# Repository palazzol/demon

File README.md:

# Demon Debugger system - 2.0 coming soon!

Debugger/Monitor for small "computers"

## Vintage Computer Festival Midwest 17 - 2022

- [YouTube](https://youtu.be/M9XML7viIT8)

- [Slides](doc/DD_Presentation-VCFMW_2022.pdf)

## Important Note

**We would like to port this to more systems, and/or help others fix their old things. Please let us know if you need any help getting this system going, should you choose to give it a try!**

## Newly added

* 68HC11 Reference Target - used for Chuck E Cheese Cyberamics computer

## New in version 2.0

* No EPROM programmer needed, reflash through USB serial
* New CPUs supported
  * 6800, 6809
* New targets supported
  * MicroProfessor-1 (Z80 trainer)
  * Heathkit ET-3400(A) (6800 trainer)
  * Heathkit ET-3404 (ET-3400(A) + 6809 adapter) (6809 trainer)
* GUI client
* Python API (alpha) for automating control of targets
* Modularized target code, less work for supporting new targets

## Description

Demon Debugger is a tool that can be used to repair and reverse-engineer devices with 8 and 16 bit CPUs, such as arcade machines, console games, embedded computers, single board computers, etc.  It provides a debugging console, and so is especially useful for systems that lack a working one.

It has been ported to Z80-based, 6502-based, 6800-based, 6809-based, and CP1610-based systems.  There are ports underway to other CPU architectures.

Unfortunately, Demon Debugger can't be used on a totally broken system.  The target system must have a working CPU, and at least a small amount of ROM and RAM.  However, we have found that for most hardware, it's really not too hard to get a system to this point.

## How it Works

In ROM I/O mode, The Demon Debugger board cable plugs into a socket on the target system, in place of a standard JEDEC ROM/EPROM chip.  Then, your PC can communicate with the target over serial, using a standard USB connection.

If your target system is already supported, there will be a target image already built, which you can upload onto your target.  

To support a totally new target system, a small amount of tweaking may need to be done to the assembly code for your target. Generally, if you know the memory map for your system, this is really easy to do.

## More Details

The Demon Debugger system has evolved over time.  If you have a Demon Debugger board, you can use ROM I/O mode with prebuilt target code, and get started right away, without any other tools.  If you need to support a new target, you can still use ROM I/O mode, once you build a new target code.

If you don't have a Demon Debugger board, you can still use the Demon Debugger system in Tethered mode, provided you have a few other capabilities.  It requires only an Arduino Nano/Uno, a single transistor, and the ability to program an EPROM chip.  You need to identify points on your target which can be used (2 outputs, 1 input, and a ground), wire up your modified Arduino accordingly, and modify the communication routines in the target to use those points.  There are a few examples in the repo of doing this.

## Currently Supported Targets

### 6502

* Generic 6502 (Works on most targets) - Atari Asteroids, VCFMW Badge!
* Atari Asteroids Arcade, tethered mode
* Atari Starship 1 Arcade

### 6800

* Heathkit ET-3400(A) (6800 trainer)

### 6809

* Heathkit ET-3404 (ET-3400(A) + 6809 adapter) (6809 trainer)
* Radio Shack Color Computer - Cartridge (6809)

### 6811

* (Chuck E. Cheese Cyberamics Computer) (6811 reference)

### Z80

* Z80 reference code (Tweakable to work on most targets)
* Sega Star Trek Arcade
* Sega Star Trek Arcade, tethered mode
* Bally Midway Gorf Arcade 
* Bally Astrocade, cartridge
* Colecovision/Bit90, cartridge
* Universal Space Raider Arcade
* MicroProfessor-1 (Z80 trainer)

### CP1610

* Mattel Intellivision - via LTO Flash cartridge*

### Other - coming soon

* Mattel Intellivision, via T-Card cartridge (CP1610 target)
* 8080/8085 targets
* Atari 2600 (6502)
* RCA1802 targets
* OS816 SBC (65C816 target)
* TI 99/4A cartridge (TMS9900 target)

## Command Line Client

## GUI Client (WIP)

## API

For now, please see the file demonapi.py

## Old Videos

Tethered Mode - [Sega Sound Board test](https://www.youtube.com/watch?v=uYlbb8uPjoU) Quality is not very good, but the Arduino module is next to the laptop

[Intellivision Demo](https://www.youtube.com/watch?v=_8YfCMpHLhY) Better quality, no Arduino needed using native serialport on the LTO Flash cart.

## 3D Rendering from KiCad

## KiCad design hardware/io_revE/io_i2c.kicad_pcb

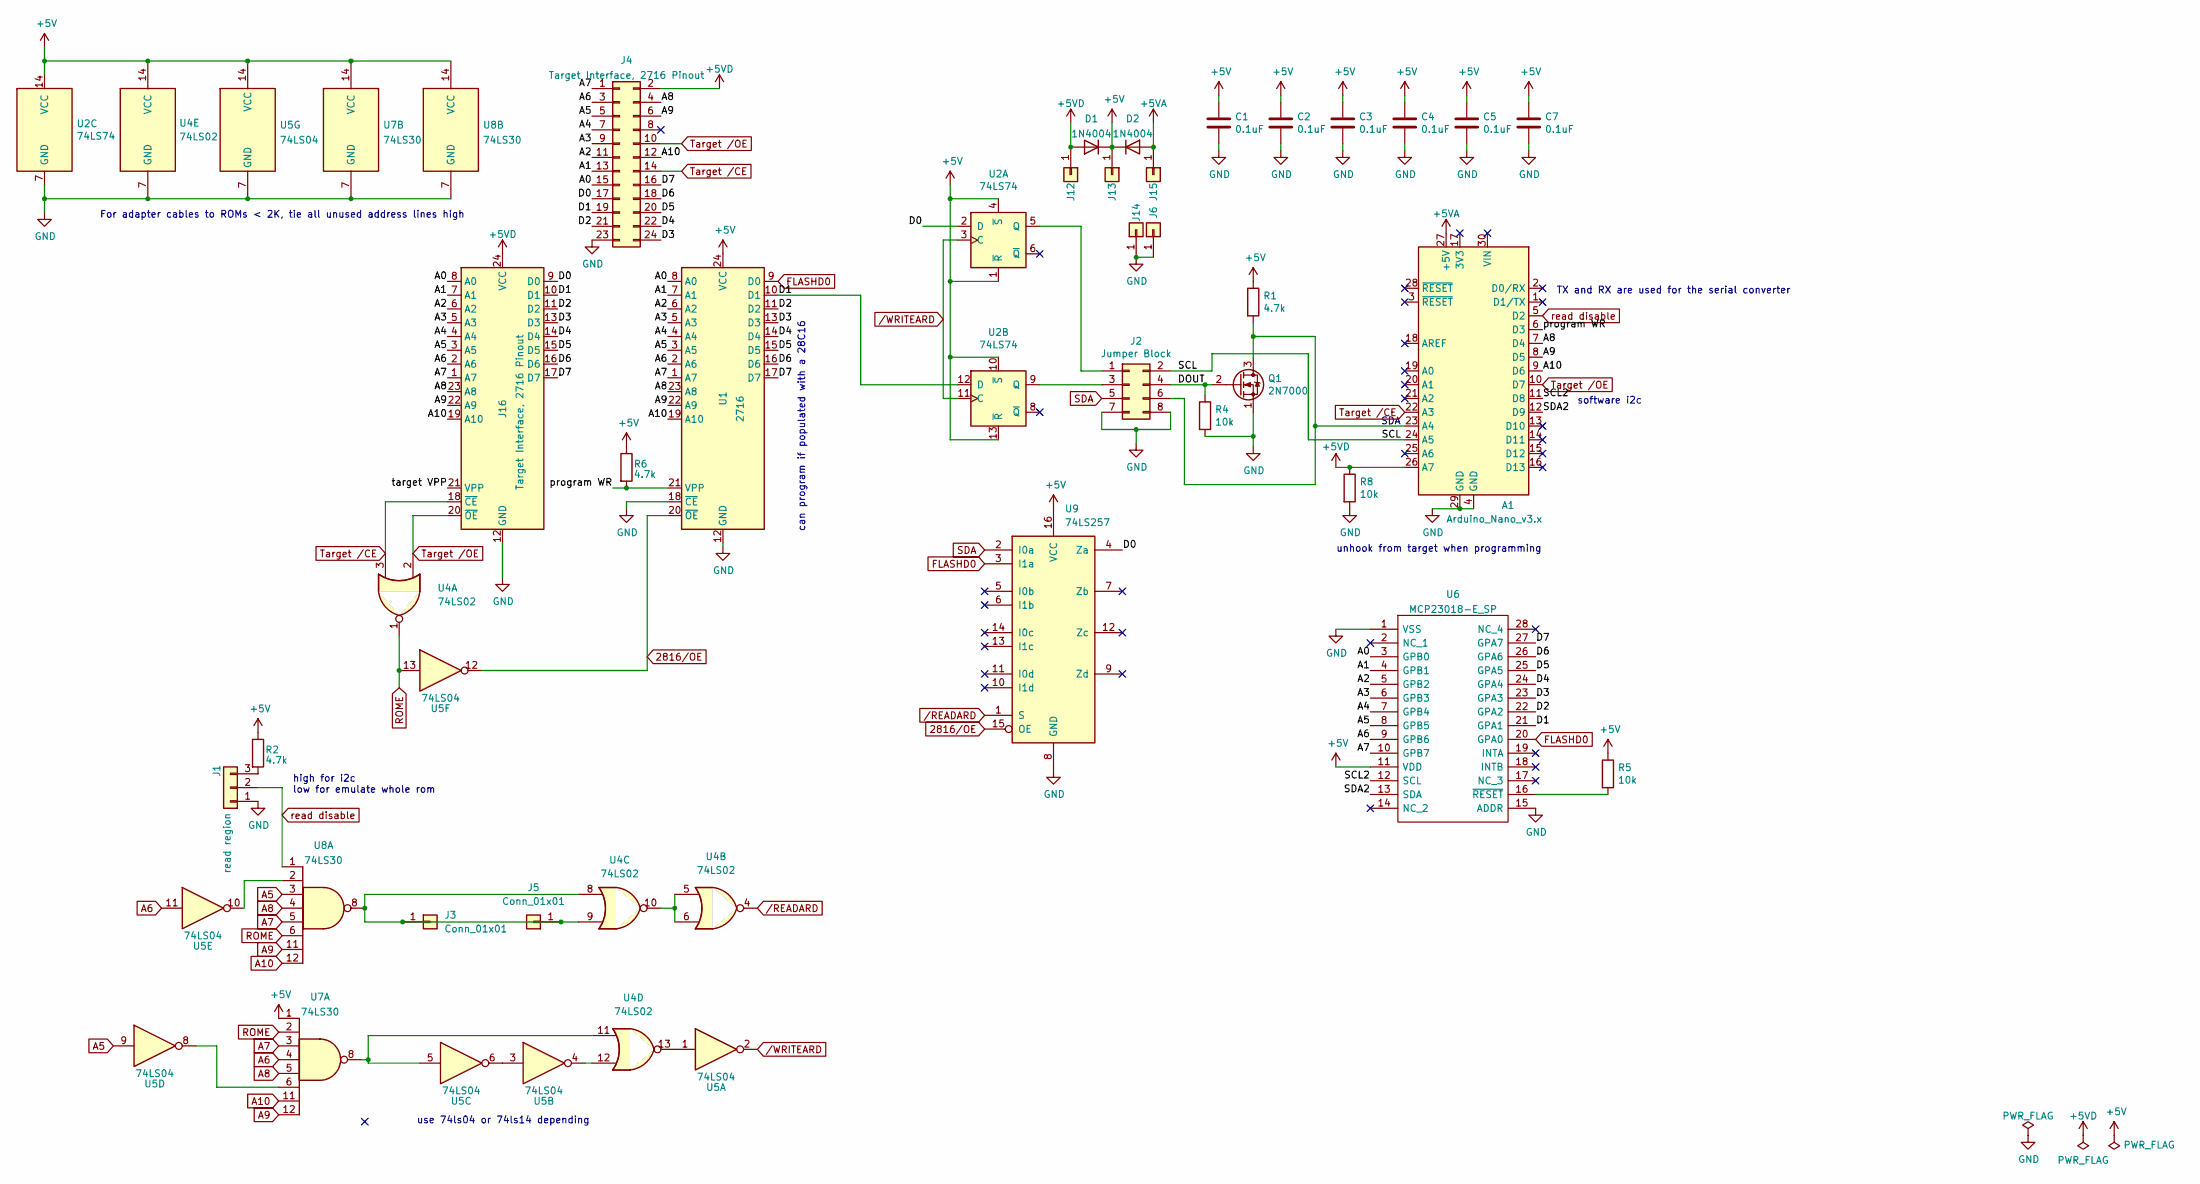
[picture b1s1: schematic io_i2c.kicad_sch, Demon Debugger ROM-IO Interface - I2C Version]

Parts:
A1: Arduino_Nano_v3.x; Arduino_Nano
C1, C2, C3, C4, C5, C7: 0.1uF; C_Axial_L3.8mm_D2.6mm_P7.50mm_Horizontal
D1, D2: 1N4004; D_DO-41_SOD81_P2.54mm_Vertical_AnodeUp
J1: read region; PinHeader_1x03_P2.54mm_Vertical
J2: Jumper Block; PinHeader_2x04_P2.54mm_Vertical
J3, J5, J6, J12, J13, J14, J15: Conn_01x01; PinHeader_1x01_P2.54mm_Vertical
J4: Target Interface, 2716 Pinout; PinHeader_2x12_P2.54mm_Vertical
J16: Target Interface, 2716 Pinout; DIP-24_W15.24mm_Socket
Q1: 2N7000; TO-92_Wide
R1, R2, R6: 4.7k; R_Axial_DIN0207_L6.3mm_D2.5mm_P2.54mm_Vertical
R4, R5, R8: 10k; R_Axial_DIN0207_L6.3mm_D2.5mm_P2.54mm_Vertical
U1: 2716; DIP-24_W15.24mm_Socket
U2: 74LS74; DIP-14_W7.62mm
U4: 74LS02; DIP-14_W7.62mm
U5: 74LS04; DIP-14_W7.62mm
U6: MCP23018-E_SP; DIP-28_W7.62mm; Mouser Part Number 579-MCP23018-E/SP
U7, U8: 74LS30; DIP-14_W7.62mm
U9: 74LS257; DIP-16_W7.62mm

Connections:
2816/OE: U1.20 (~OE), U5.12, U9.15 (OE)
+5V: C1.1, C2.1, C3.1, C4.1, C5.1, C7.1, D1.1 (K), D2.1 (K), J13.1 (Pin_1_1), R1.1, R2.1, R5.1, R6.1, U1.24 (VCC), U2.1 (~R), U2.4 (~S), U2.10 (~S), U2.13 (~R), U2.14 (VCC), U4.14 (VCC), U5.14 (VCC), U6.11 (VDD), U7.1, U7.14 (VCC), U8.14 (VCC), U9.16 (VCC)
+5VA: A1.27 (+5V), D2.2 (A), J15.1 (Pin_1_1)
+5VD: A1.26 (A7), D1.2 (A), J4.2, J12.1 (Pin_1_1), J16.24 (VCC), R8.1
/A0: J4.15, J16.8 (A0), U1.8 (A0), U6.3 (GPB0)
/A1: J4.13, J16.7 (A1), U1.7 (A1), U6.4 (GPB1)
/A2: J4.11, J16.6 (A2), U1.6 (A2), U6.5 (GPB2)
/A3: J4.9, J16.5 (A3), U1.5 (A3), U6.6 (GPB3)
/A4: J4.7, J16.4 (A4), U1.4 (A4), U6.7 (GPB4)
/D0: J4.17, J16.9 (D0), U2.2 (D), U9.4 (Za)
/D1: J4.19, J16.10 (D1), U1.10 (D1), U2.12 (D), U6.21 (GPA1)
/D2: J4.21, J16.11 (D2), U1.11 (D2), U6.22 (GPA2)
/D3: J4.24, J16.13 (D3), U1.13 (D3), U6.23 (GPA3)
/D4: J4.22, J16.14 (D4), U1.14 (D4), U6.24 (GPA4)
/D5: J4.20, J16.15 (D5), U1.15 (D5), U6.25 (GPA5)
/D6: J4.18, J16.16 (D6), U1.16 (D6), U6.26 (GPA6)
/D7: J4.16, J16.17 (D7), U1.17 (D7), U6.27 (GPA7)
/DOUT: J2.4, Q1.2 (G), R4.1
/SCL: A1.24 (A5), J2.2
/SCL2: A1.11 (D8), U6.12 (SCL)
/SDA2: A1.12 (D9), U6.13 (SDA)
/program WR: A1.6 (D3), R6.2, U1.21 (VPP)
/target VPP: J16.21 (VPP)
A5: J4.5, J16.3 (A5), U1.3 (A5), U5.9, U6.8 (GPB5), U8.3
A6: J4.3, J16.2 (A6), U1.2 (A6), U5.11, U6.9 (GPB6), U7.4
A7: J4.1, J16.1 (A7), U1.1 (A7), U6.10 (GPB7), U7.3, U8.5
A8: A1.7 (D4), J4.4, J16.23 (A8), U1.23 (A8), U7.5, U8.4
A9: A1.8 (D5), J4.6, J16.22 (A9), U1.22 (A9), U7.12, U8.11
A10: A1.9 (D6), J4.12, J16.19 (A10), U1.19 (A10), U7.11, U8.12
FLASHD0: U1.9 (D0), U6.20 (GPA0), U9.3 (I1a)
GND: A1.4 (GND), A1.29 (GND), C1.2, C2.2, C3.2, C4.2, C5.2, C7.2, J1.1, J2.7, J2.8, J4.23, J6.1 (Pin_1_1), J14.1 (Pin_1_1), J16.12 (GND), Q1.1 (S), R4.2, R8.2, U1.12 (GND), U1.18 (~CE), U2.7 (GND), U4.7 (GND), U5.7 (GND), U6.1 (VSS), U6.15 (ADDR), U7.7 (GND), U8.7 (GND), U9.8 (GND)
unnamed: A1.23 (A4), J2.6, Q1.3 (D), R1.2
unnamed: J1.3, R2.2
unnamed: J2.1, U2.5 (Q)
unnamed: J2.3, U2.9 (Q)
unnamed: J3.1 (Pin_1_1), J5.1 (Pin_1_1), U4.8, U4.9, U8.8
unnamed: U4.5, U4.6, U4.10
unnamed: U4.11, U5.5, U7.8
unnamed: U4.12, U5.4
unnamed: U4.13, U5.1
unnamed: U5.3, U5.6
unnamed: U5.8, U7.6
unnamed: U5.10, U8.2
unnamed: R5.2, U6.16 (~RESET)
ROME: U4.1, U5.13, U7.2, U8.6
SDA: J2.5, U9.2 (I0a)
Target /CE: A1.22 (A3), J4.14, J16.18 (~CE), U4.3
Target /OE: A1.10 (D7), J4.10, J16.20 (~OE), U4.2
read disable: A1.5 (D2), J1.2, U8.1
/READARD: U4.4, U9.1 (S)
/WRITEARD: U2.3 (C), U2.11 (C), U5.2

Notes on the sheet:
TX and RX are used for the serial converter
For adapter cables to ROMs < 2K, tie all unused address lines high
can program if populated with a 28C16
high for i2c low for emulate whole rom
use 74ls04 or 74ls14 depending
SDA
unhook from target when programming
software i2c

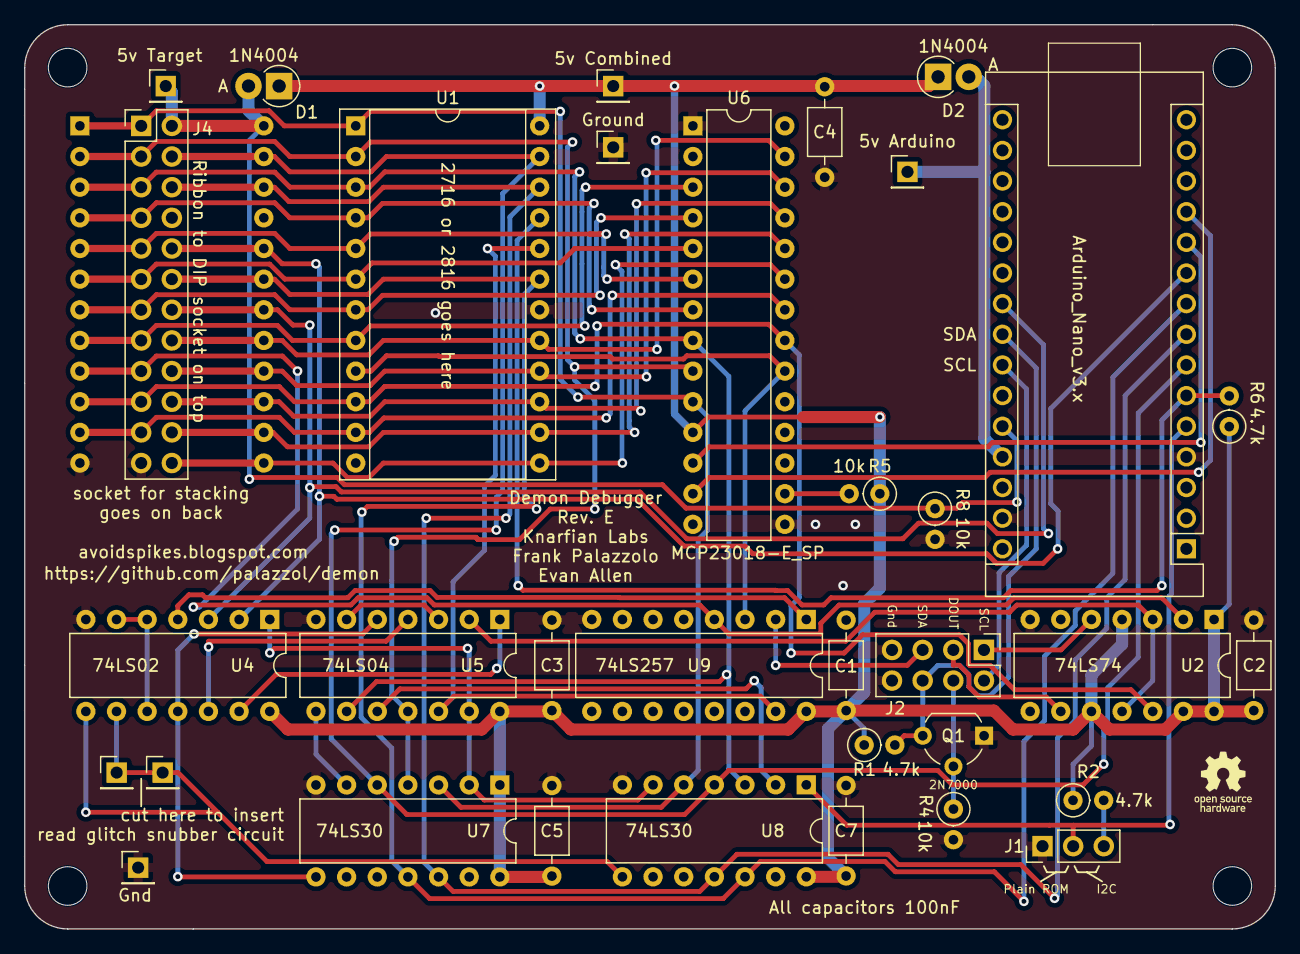
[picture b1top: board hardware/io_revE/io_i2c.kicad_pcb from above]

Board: 2 copper layers, 103.6 x 74.9 mm, 35 parts (0 on the bottom side), 50 nets.

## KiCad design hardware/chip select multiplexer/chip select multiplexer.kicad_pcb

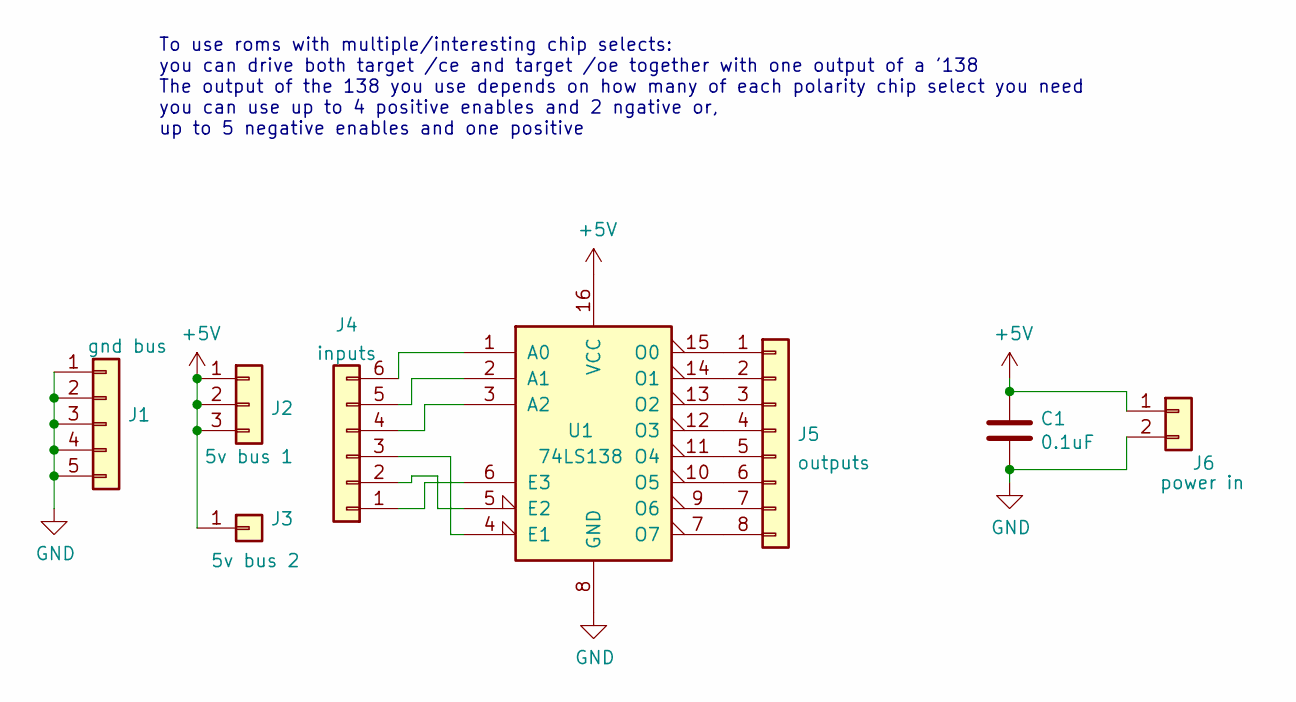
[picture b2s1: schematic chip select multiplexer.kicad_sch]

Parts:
C1: 0.1uF; C_Axial_L3.8mm_D2.6mm_P7.50mm_Horizontal
J1: gnd bus; PinHeader_1x05_P2.54mm_Vertical
J2: 5v bus 1; PinHeader_1x03_P2.54mm_Vertical
J3: 5v bus 2; PinHeader_1x01_P2.54mm_Vertical
J4: inputs; PinHeader_1x06_P2.54mm_Vertical
J5: outputs; PinHeader_1x08_P2.54mm_Vertical
J6: power in; PinHeader_1x02_P2.54mm_Vertical
U1: 74LS138; DIP-16_W7.62mm

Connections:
+5V: C1.1, J2.1, J2.2, J2.3, J3.1, J6.1, U1.16 (VCC)
GND: C1.2, J1.1, J1.2, J1.3, J1.4, J1.5, J6.2, U1.8 (GND)
unnamed: J4.1, U1.6 (E3)
unnamed: J4.2, U1.5 (E2)
unnamed: J4.3, U1.4 (E1)
unnamed: J4.4, U1.3 (A2)
unnamed: J4.5, U1.2 (A1)
unnamed: J4.6, U1.1 (A0)
unnamed: J5.1, U1.15 (O0)
unnamed: J5.2, U1.14 (O1)
unnamed: J5.3, U1.13 (O2)
unnamed: J5.4, U1.12 (O3)
unnamed: J5.5, U1.11 (O4)
unnamed: J5.6, U1.10 (O5)
unnamed: J5.7, U1.9 (O6)
unnamed: J5.8, U1.7 (O7)

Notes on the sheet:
To use roms with multiple/interesting chip selects: you can drive both target /ce and target /oe together with one output of a '138 The output of the 138 you use depends on how many of each polarity chip select you need you can use up to 4 positive enables and 2 ngative or, up to 5 negative enables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

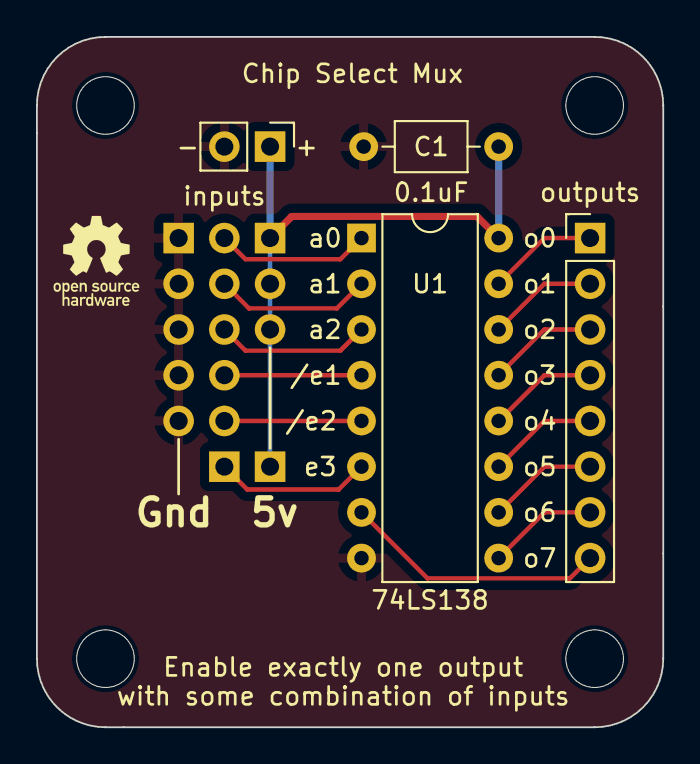
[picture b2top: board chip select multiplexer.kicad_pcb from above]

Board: 2 copper layers, 34.8 x 38.4 mm, 8 parts (0 on the bottom side), 16 nets.

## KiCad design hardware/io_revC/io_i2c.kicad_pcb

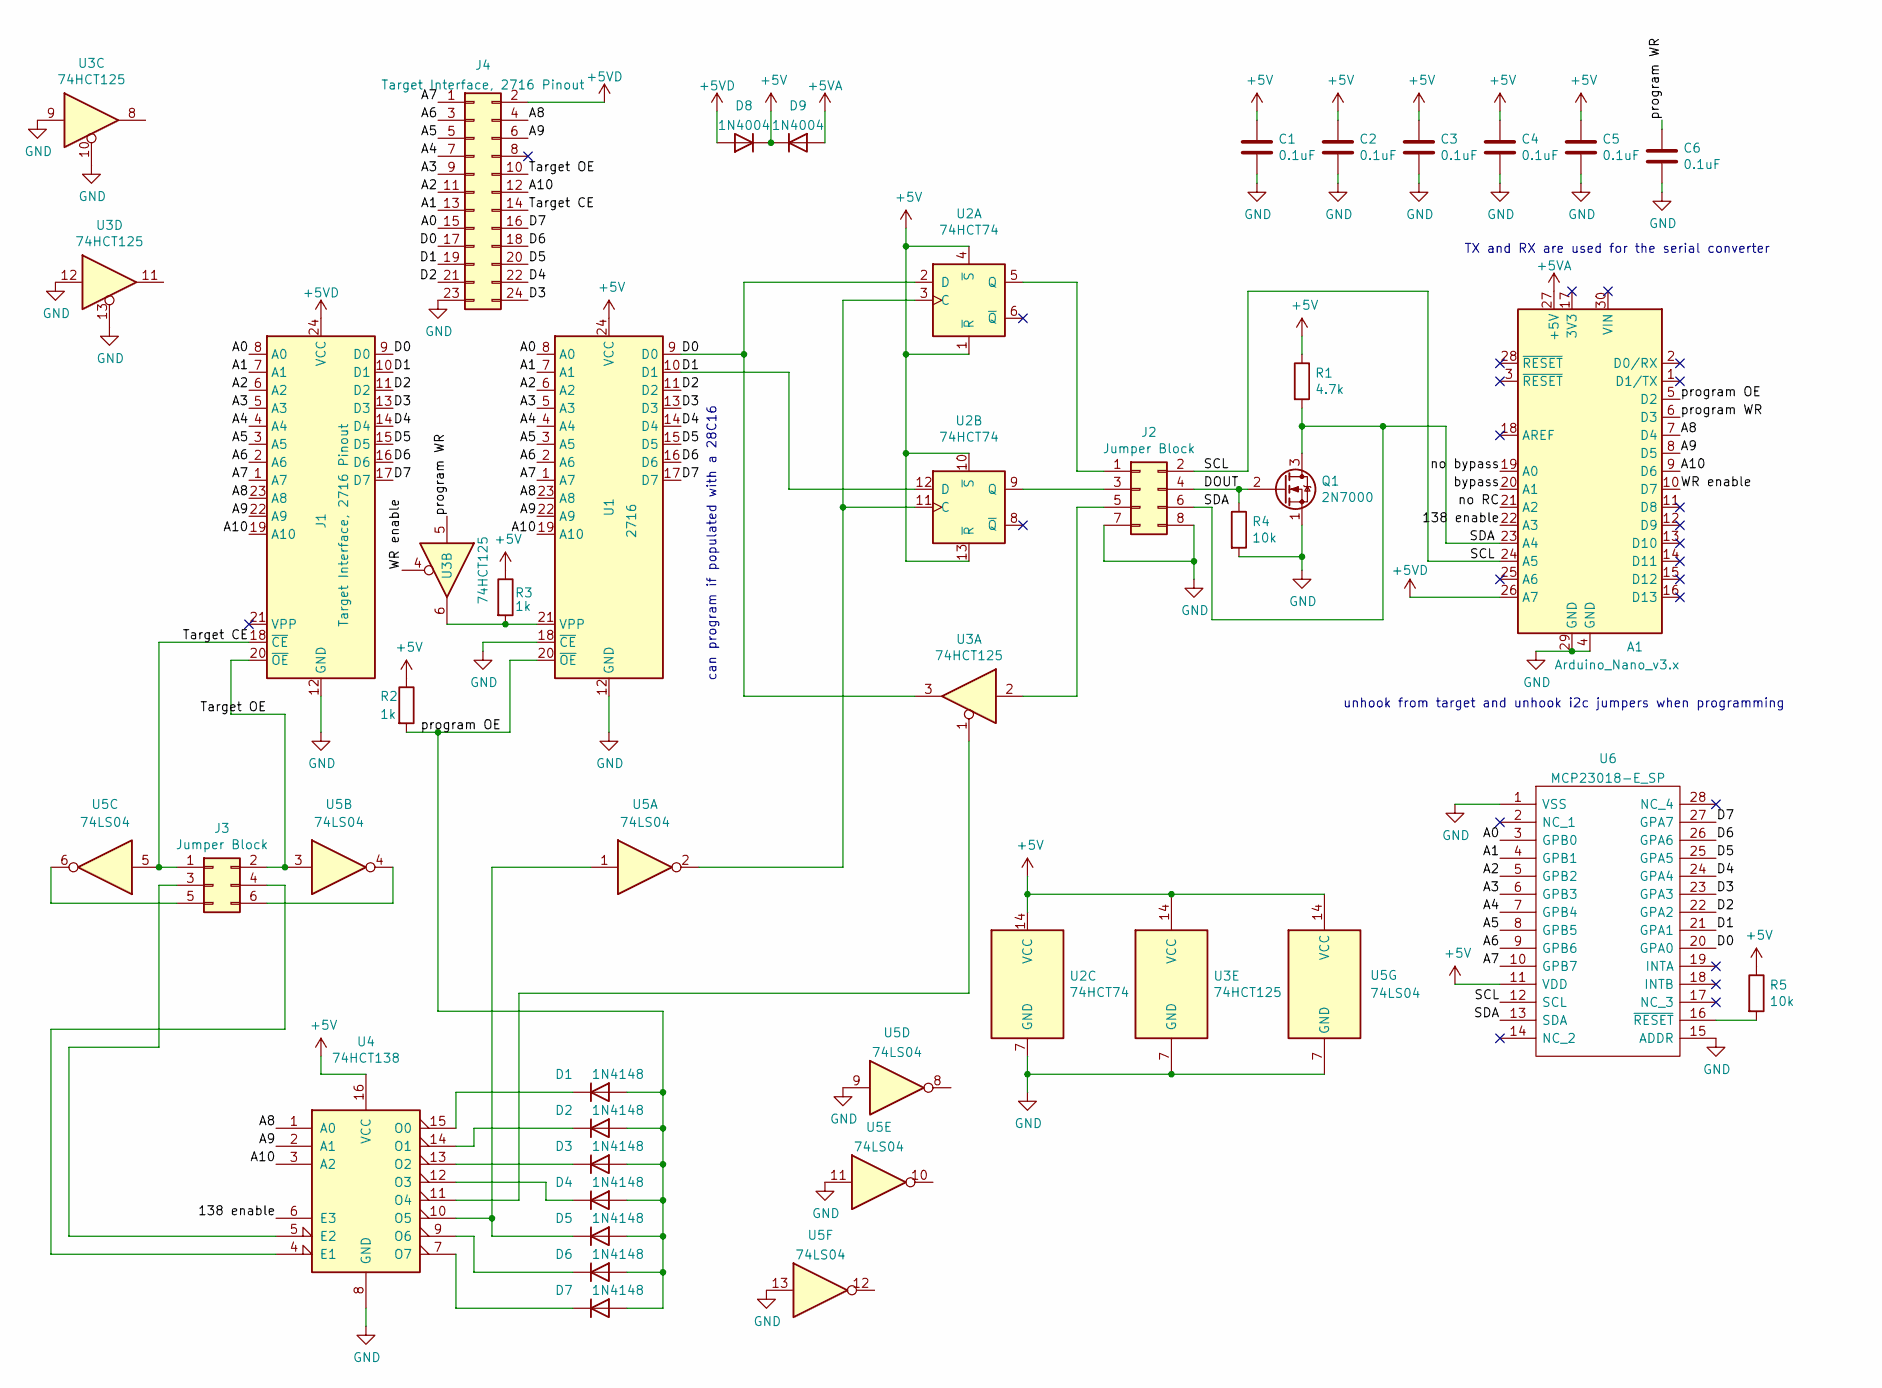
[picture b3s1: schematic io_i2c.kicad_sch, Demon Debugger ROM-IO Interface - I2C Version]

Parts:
A1: Arduino_Nano_v3.x; Arduino_Nano
C1, C2, C3, C4, C5: 0.1uF; C_Axial_L3.8mm_D2.6mm_P7.50mm_Horizontal
C6: 0.1uF; C_0603_1608Metric
D1, D2, D3, D4, D5, D6, D7: 1N4148; D_DO-35_SOD27_P2.54mm_Vertical_AnodeUp
D8, D9: 1N4004; D_DO-41_SOD81_P2.54mm_Vertical_AnodeUp
J1: Target Interface, 2716 Pinout; DIP-24_W15.24mm_Socket
J2: Jumper Block; PinHeader_2x04_P2.54mm_Vertical
J3: Jumper Block; PinHeader_2x03_P2.54mm_Vertical
J4: Target Interface, 2716 Pinout; PinHeader_2x12_P2.54mm_Vertical
Q1: 2N7000; TO-92_Inline
R1: 4.7k; R_Axial_DIN0207_L6.3mm_D2.5mm_P2.54mm_Vertical
R2, R3: 1k; R_Axial_DIN0207_L6.3mm_D2.5mm_P2.54mm_Vertical
R4, R5: 10k; R_Axial_DIN0207_L6.3mm_D2.5mm_P2.54mm_Vertical
U1: 2716; DIP-24_W15.24mm_Socket
U2: 74HCT74; DIP-14_W7.62mm
U3: 74HCT125; DIP-14_W7.62mm
U4: 74HCT138; DIP-16_W7.62mm
U5: 74LS04
U6: MCP23018-E_SP; DIP-28_W7.62mm; Mouser Part Number 579-MCP23018-E/SP

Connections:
+5V: C1.1, C2.1, C3.1, C4.1, C5.1, D8.1 (K), D9.1 (K), R1.1, R2.1, R3.1, R5.1, U1.24 (VCC), U2.1 (~R), U2.4 (~S), U2.10 (~S), U2.13 (~R), U2.14 (VCC), U3.14 (VCC), U4.16 (VCC), U5.14 (VCC), U6.11 (VDD)
+5VA: A1.27 (+5V), D9.2 (A)
+5VD: A1.26 (A7), D8.2 (A), J1.24 (VCC), J4.2
/138 enable: A1.22 (A3), U4.6 (E3)
/A0: J1.8 (A0), J4.15, U1.8 (A0), U6.3 (GPB0)
/A1: J1.7 (A1), J4.13, U1.7 (A1), U6.4 (GPB1)
/A2: J1.6 (A2), J4.11, U1.6 (A2), U6.5 (GPB2)
/A3: J1.5 (A3), J4.9, U1.5 (A3), U6.6 (GPB3)
/A4: J1.4 (A4), J4.7, U1.4 (A4), U6.7 (GPB4)
/A5: J1.3 (A5), J4.5, U1.3 (A5), U6.8 (GPB5)
/A6: J1.2 (A6), J4.3, U1.2 (A6), U6.9 (GPB6)
/A7: J1.1 (A7), J4.1, U1.1 (A7), U6.10 (GPB7)
/A8: A1.7 (D4), J1.23 (A8), J4.4, U1.23 (A8), U4.1 (A0)
/A9: A1.8 (D5), J1.22 (A9), J4.6, U1.22 (A9), U4.2 (A1)
/A10: A1.9 (D6), J1.19 (A10), J4.12, U1.19 (A10), U4.3 (A2)
/D0: J1.9 (D0), J4.17, U1.9 (D0), U2.2 (D), U3.3, U6.20 (GPA0)
/D1: J1.10 (D1), J4.19, U1.10 (D1), U2.12 (D), U6.21 (GPA1)
/D2: J1.11 (D2), J4.21, U1.11 (D2), U6.22 (GPA2)
/D3: J1.13 (D3), J4.24, U1.13 (D3), U6.23 (GPA3)
/D4: J1.14 (D4), J4.22, U1.14 (D4), U6.24 (GPA4)
/D5: J1.15 (D5), J4.20, U1.15 (D5), U6.25 (GPA5)
/D6: J1.16 (D6), J4.18, U1.16 (D6), U6.26 (GPA6)
/D7: J1.17 (D7), J4.16, U1.17 (D7), U6.27 (GPA7)
/DOUT: J2.4, Q1.2 (G), R4.1
/SCL: A1.24 (A5), J2.2, U6.12 (SCL)
/SDA: A1.23 (A4), J2.6, Q1.3 (D), R1.2, U6.13 (SDA)
/Target CE: J1.18 (~CE), J3.1, J4.14, U5.5
/Target OE: J1.20 (~OE), J3.2, J4.10, U5.3
/WR enable: A1.10 (D7), U3.4
/bypass: A1.20 (A1)
/no RC: A1.21 (A2)
/no bypass: A1.19 (A0)
/program OE: A1.5 (D2), D1.2 (A), D2.2 (A), D3.2 (A), D4.2 (A), D5.2 (A), D6.2 (A), D7.2 (A), R2.2, U1.20 (~OE)
/program WR: A1.6 (D3), C6.1, U3.5
GND: A1.4 (GND), A1.29 (GND), C1.2, C2.2, C3.2, C4.2, C5.2, C6.2, J1.12 (GND), J2.7, J2.8, J4.23, Q1.1 (S), R4.2, U1.12 (GND), U1.18 (~CE), U2.7 (GND), U3.7 (GND), U3.9, U3.10, U3.12, U3.13, U4.8 (GND), U5.7 (GND), U5.9, U5.11, U5.13, U6.1 (VSS), U6.15 (ADDR)
unnamed: D1.1 (K), U4.15 (O0)
unnamed: D2.1 (K), U4.14 (O1)
unnamed: D3.1 (K), U4.13 (O2)
unnamed: D4.1 (K), U4.12 (O3)
unnamed: D5.1 (K), U4.10 (O5), U5.1
unnamed: D6.1 (K), U4.9 (O6)
unnamed: D7.1 (K), U4.7 (O7)
unnamed: J2.1, U2.5 (Q)
unnamed: J2.3, U2.9 (Q)
unnamed: J2.5, U3.2
unnamed: J3.3, U4.5 (E2)
unnamed: J3.4, U4.4 (E1)
unnamed: J3.5, U5.6
unnamed: J3.6, U5.4
unnamed: R3.2, U1.21 (VPP), U3.6
unnamed: R5.2, U6.16 (~RESET)
unnamed: U2.3 (C), U2.11 (C), U5.2
unnamed: U3.1, U4.11 (O4)

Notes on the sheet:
TX and RX are used for the serial converter
can program if populated with a 28C16
unhook from target and unhook i2c jumpers when programming

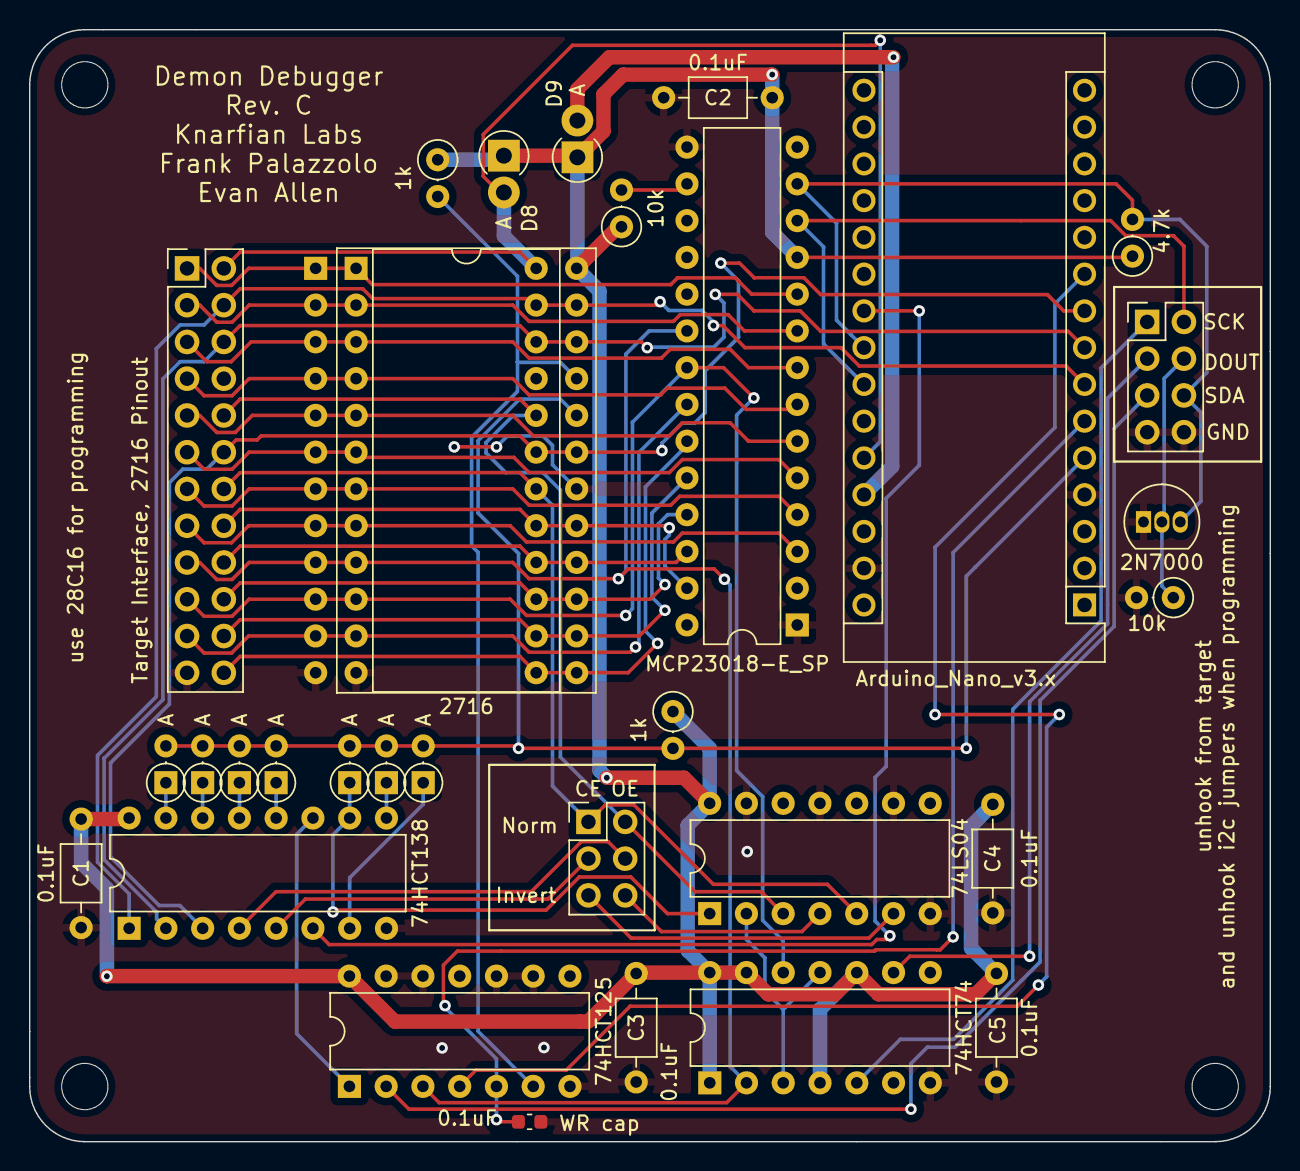
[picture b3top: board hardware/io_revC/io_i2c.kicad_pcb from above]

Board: 2 copper layers, 85.7 x 76.8 mm, 32 parts (0 on the bottom side), 50 nets.

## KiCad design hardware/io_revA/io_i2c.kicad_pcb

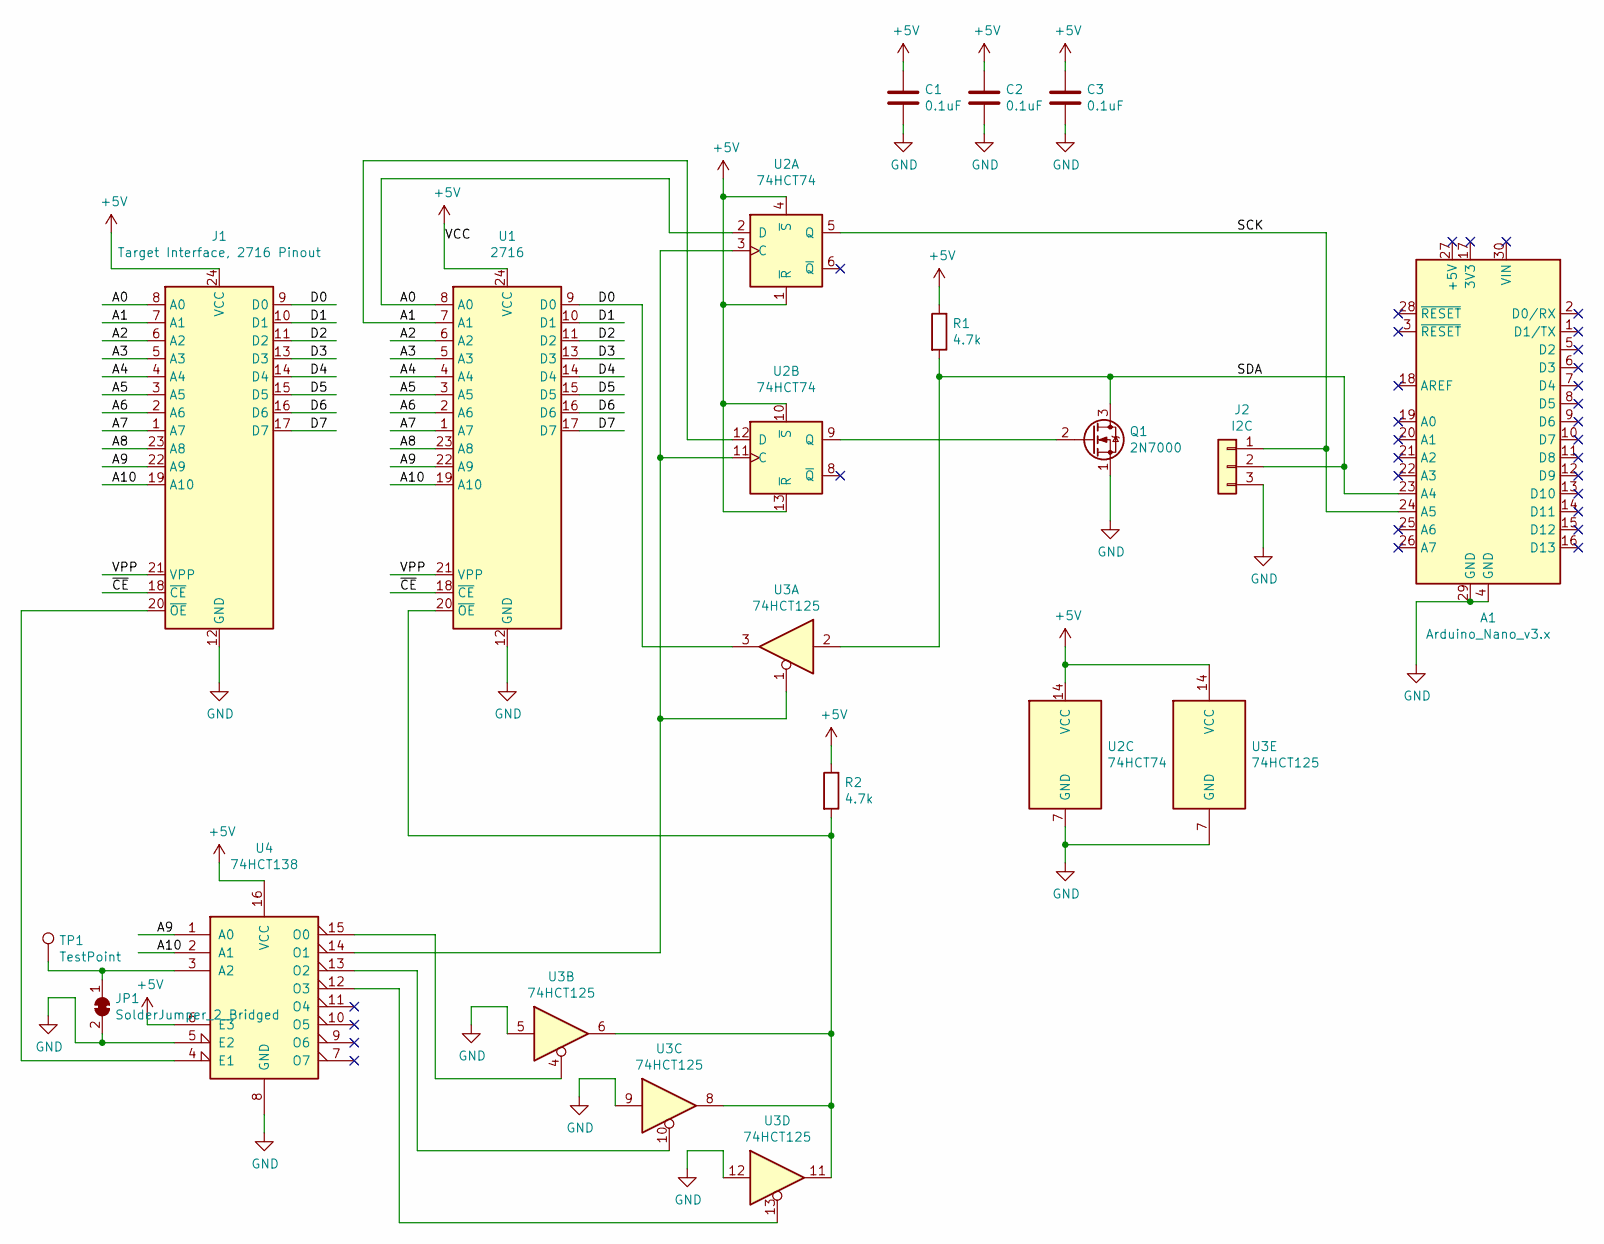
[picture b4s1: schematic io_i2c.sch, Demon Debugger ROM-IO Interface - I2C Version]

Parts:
A1: Arduino_Nano_v3.x; Arduino_Nano
C1, C2, C3: 0.1uF; C_Axial_L3.8mm_D2.6mm_P7.50mm_Horizontal
J1: Target Interface, 2716 Pinout; DIP-24_W15.24mm_Socket
J2: I2C; PinHeader_1x03_P2.54mm_Vertical
JP1: SolderJumper_2_Bridged; SolderJumper-2_P1.3mm_Bridged_RoundedPad1.0x1.5mm
Q1: 2N7000; TO-92_Inline
R1, R2: 4.7k; R_Axial_DIN0207_L6.3mm_D2.5mm_P10.16mm_Horizontal
TP1: TestPoint; TestPoint_THTPad_D1.5mm_Drill0.7mm
U1: 2716; DIP-24_W15.24mm_Socket
U2: 74HCT74; DIP-14_W7.62mm
U3: 74HCT125; DIP-14_W7.62mm
U4: 74HCT138; DIP-16_W7.62mm

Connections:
+5V: C1.1, C2.1, C3.1, J1.24 (VCC), R1.1, R2.1, U1.24 (VCC), U2.1 (~R), U2.4 (~S), U2.10 (~S), U2.13 (~R), U2.14 (VCC), U3.14 (VCC), U4.6 (E3), U4.16 (VCC)
/A0: J1.8 (A0), U1.8 (A0), U2.2 (D)
/A1: J1.7 (A1), U1.7 (A1), U2.12 (D)
/A2: J1.6 (A2), U1.6 (A2)
/A3: J1.5 (A3), U1.5 (A3)
/A4: J1.4 (A4), U1.4 (A4)
/A5: J1.3 (A5), U1.3 (A5)
/A6: J1.2 (A6), U1.2 (A6)
/A7: J1.1 (A7), U1.1 (A7)
/A8: J1.23 (A8), U1.23 (A8)
/A9: J1.22 (A9), U1.22 (A9), U4.1 (A0)
/A10: J1.19 (A10), U1.19 (A10), U4.2 (A1)
/D0: J1.9 (D0), U1.9 (D0), U3.3
/D1: J1.10 (D1), U1.10 (D1)
/D2: J1.11 (D2), U1.11 (D2)
/D3: J1.13 (D3), U1.13 (D3)
/D4: J1.14 (D4), U1.14 (D4)
/D5: J1.15 (D5), U1.15 (D5)
/D6: J1.16 (D6), U1.16 (D6)
/D7: J1.17 (D7), U1.17 (D7)
/SCK: A1.24 (A5), J2.1, U2.5 (Q)
/SDA: A1.23 (A4), J2.2, Q1.3 (D), R1.2, U3.2
/VPP: J1.21 (VPP), U1.21 (VPP)
/~CE: J1.18 (~CE), U1.18 (~CE)
GND: A1.4 (GND), A1.29 (GND), C1.2, C2.2, C3.2, J1.12 (GND), J2.3, JP1.2 (B), Q1.1 (S), U1.12 (GND), U2.7 (GND), U3.5, U3.7 (GND), U3.9, U3.12, U4.5 (E2), U4.8 (GND)
unnamed: J1.20 (~OE), U4.4 (E1)
unnamed: JP1.1 (A), TP1.1, U4.3 (A2)
unnamed: Q1.2 (G), U2.9 (Q)
unnamed: R2.2, U1.20 (~OE), U3.6, U3.8, U3.11
unnamed: U2.3 (C), U2.11 (C), U3.1, U4.14 (O1)
unnamed: U3.4, U4.15 (O0)
unnamed: U3.10, U4.13 (O2)
unnamed: U3.13, U4.12 (O3)

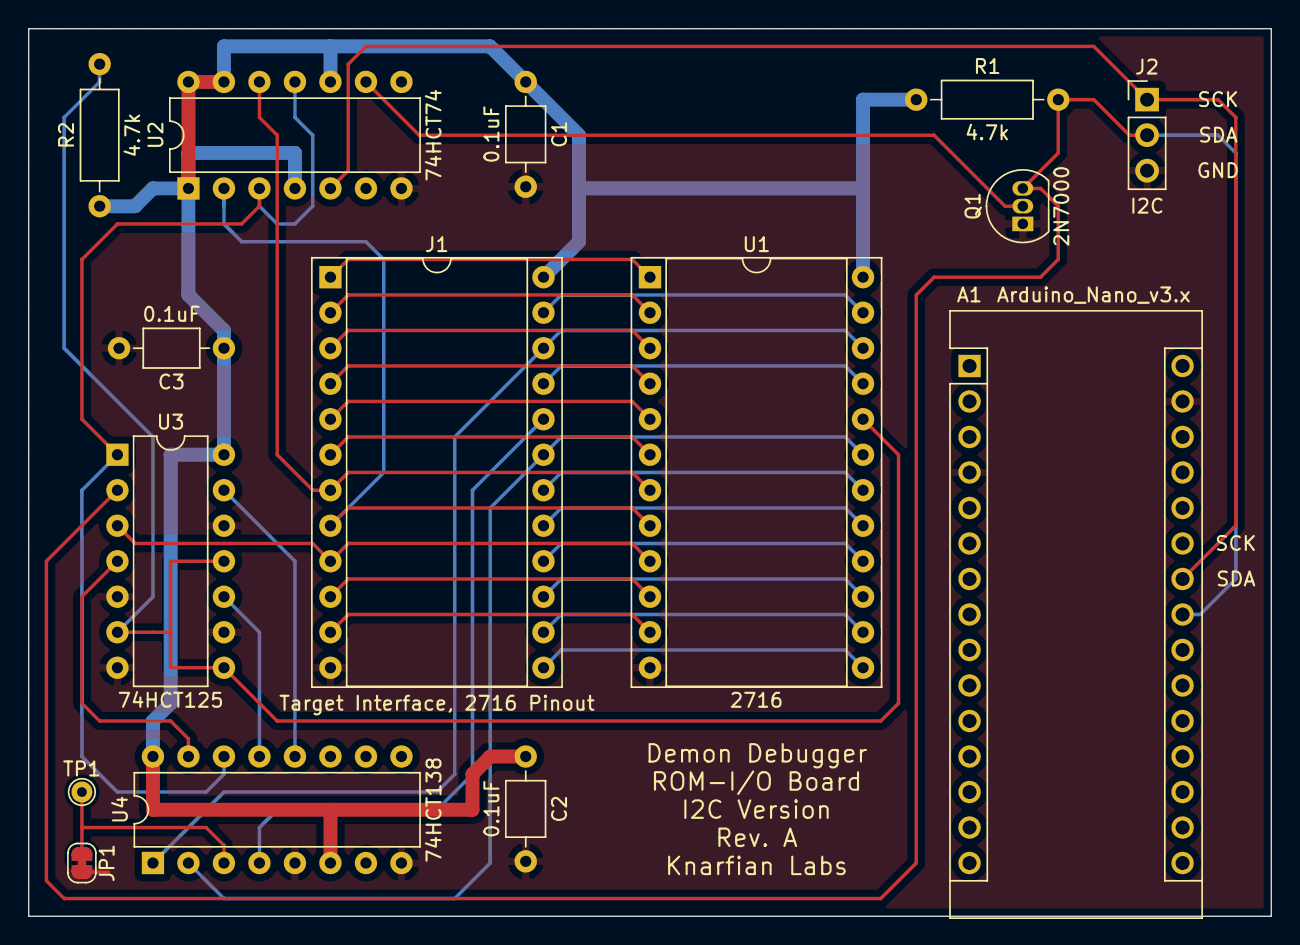
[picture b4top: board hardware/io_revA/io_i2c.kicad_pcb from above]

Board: 2 copper layers, 88.9 x 63.5 mm, 15 parts (0 on the bottom side), 33 nets.
